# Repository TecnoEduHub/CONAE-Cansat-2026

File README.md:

# CANSAT 2026 — E.E.S.T. N.º5 "Amancio Williams"

Repositorio destinado a documentar el proceso de participación de la **Escuela de Educación Secundaria Técnica N.º 5 "Amancio Williams" de Mar del Plata** en el **Certamen CANSAT Secundario 2026**, organizado por la **Comisión Nacional de Actividades Espaciales (CONAE)**.

Este repositorio tiene como objetivo conservar el registro del proceso realizado por los estudiantes y docentes de la Técnica N.º 5.

La documentación irá incorporando progresivamente:

- Diseño conceptual.
- Documento Preliminar de Diseño.
- Investigación y antecedentes.
- Diseño electrónico.
- Programación y firmware.
- Diseño mecánico.
- Sistema de descenso.
- Misión primaria.
- Misión secundaria.
- Pruebas y validaciones.
- Fotografías y videos.
- Informes de avance.
- Problemas encontrados y soluciones adoptadas.
- Presentaciones y material de difusión.

La intención es que el repositorio no sea solamente un lugar donde almacenar el resultado final, sino una **bitácora técnica y educativa del proceso de aprendizaje**.

Durante la convocatoria, nuestra institución estuvo representada por dos equipos:

| Equipo | Resultado |
|---|---|
| **A.N.T.I.R.** | Actualmente en la **Etapa 4 — Construcción, seguimiento y validación** |
| **PENTA Space** | Llegó a la **Etapa 3 — Selección de proyectos y recepción del kit** |

Ambos equipos realizaron un excelente trabajo a lo largo de la competencia, atravesando un proceso de aprendizaje que involucró ciencia, electrónica, programación, diseño, experimentación, documentación y trabajo en equipo.

## ¿Qué es CANSAT?

**CANSAT** es una iniciativa educativa vinculada al ámbito espacial que propone a estudiantes de escuela secundaria asumir el desafío de diseñar, construir, probar y operar un **satélite a escala**.

El nombre surge de la combinación de las palabras **CAN** (lata) y **SAT** (satélite), debido a que la carga útil debe estar contenida dentro de un volumen aproximadamente equivalente al de una lata de gaseosa.

En Argentina, la convocatoria es organizada por la **Comisión Nacional de Actividades Espaciales (CONAE)** y busca acercar la ciencia y la tecnología a estudiantes de todo el país. El desafío reproduce, a pequeña escala, distintas etapas de una misión espacial: desde la concepción y el diseño hasta la construcción, validación, lanzamiento y operación del sistema.

Además del desarrollo tecnológico, la propuesta busca fortalecer competencias relacionadas con las disciplinas **STEM —Ciencia, Tecnología, Ingeniería y Matemáticas—**, promover el pensamiento científico y favorecer el trabajo colaborativo.

## El desafío

Cada equipo debe desarrollar una **carga útil** de dimensiones reducidas, contenida dentro de un cilindro de aproximadamente el tamaño de una lata.

El CANSAT es transportado mediante un cohete hasta una determinada altura y posteriormente desciende mediante un sistema de descenso controlado, generalmente un paracaídas. Durante el descenso debe realizar mediciones y transmitir los datos correspondientes a la misión.

La **misión primaria** establecida para CANSAT 2026 consiste en realizar, durante el descenso, un **sondeo atmosférico de presión y temperatura**.

La convocatoria también contempla una **misión secundaria**, mediante la cual cada equipo puede incorporar una actividad adicional. Para esta edición se propuso como objetivo la obtención de una imagen o video durante el lanzamiento, apogeo y/o trayectoria de descenso.

El desafío no consiste únicamente en construir un dispositivo electrónico. Los estudiantes deben trabajar como un verdadero equipo de misión: investigar, diseñar, programar, construir, documentar, realizar pruebas, analizar resultados y comunicar sus decisiones técnicas.

## Etapas de la convocatoria

La competencia se estructura en **cinco etapas eliminatorias**. Cada instancia debe ser aprobada para poder avanzar a la siguiente.

### Etapa 1 — Capacitación

Los estudiantes y docentes participan de una capacitación virtual destinada a incorporar los conocimientos, herramientas y materiales necesarios para desarrollar el proyecto.

La capacitación combina contenidos asincrónicos con instancias sincrónicas y finaliza con una evaluación.

### Etapa 2 — Diseño y presentación del proyecto

Cada equipo debe elaborar y presentar su propuesta.

Entre los principales entregables se encuentran:

- **Documento Preliminar de Diseño (DPD)**.
- **Video de presentación del equipo**.
- Descripción de la misión primaria y secundaria.
- Organización y roles de los integrantes.

La evaluación considera tanto el proyecto técnico como la capacidad del equipo para comunicar sus ideas.

### Etapa 3 — Selección y kit de materiales

Los proyectos son evaluados por un jurado y se seleccionan aquellos que resultan factibles, originales y que evidencian el compromiso y la capacidad de los equipos.

Los proyectos seleccionados reciben un **kit de materiales** para continuar con la construcción del CANSAT.

**Llegada del kit de materiales de CONAE a nuestra escuela.**

### Etapa 4 — Construcción, seguimiento y validación

Los equipos seleccionados construyen el prototipo diseñado y deben presentar diferentes evidencias de avance, incluyendo documentación, fotografías, videos y otros materiales solicitados.

Al finalizar esta instancia se realiza una validación mediante una videollamada con especialistas, en la que se presenta el prototipo y se revisa su funcionamiento.

De esta instancia se seleccionan los **cinco equipos** que participan de la campaña de lanzamiento, además de las correspondientes menciones especiales.

### Etapa 5 — Campaña de lanzamiento

Los cinco equipos seleccionados participan de la campaña de lanzamiento de sus CANSAT y realizan las mediciones correspondientes.

La convocatoria establece que los equipos seleccionados reciben cobertura de transporte, alojamiento y pensión completa para estudiantes y docentes responsables. 

## Nuestra participación

La Técnica N.º 5 tuvo la posibilidad de presentar **dos equipos** en CANSAT 2026, alcanzando ambos un desempeño destacado.

La convocatoria permite la participación de hasta dos equipos por institución. Cada equipo debe estar integrado por entre tres y cinco estudiantes y contar con el acompañamiento de un docente responsable.

### Equipo A.N.T.I.R.

**A.N.T.I.R.** es uno de los equipos representantes de la Escuela de Educación Secundaria Técnica N.º 5 "Amancio Williams".

El equipo actualmente logró avanzar hasta la:

> **Etapa 4 — Construcción, seguimiento y validación de los CANSAT**

Esto implicó superar las etapas iniciales de capacitación, presentación del proyecto y selección de propuestas, para luego recibir el kit de materiales y avanzar en la construcción y validación del prototipo.

En esta etapa el trabajo pasó del diseño conceptual a la implementación concreta: integración de hardware, programación, construcción mecánica, pruebas, documentación y preparación de las evidencias solicitadas por CONAE.

## Equipo PENTA Space

**PENTA Space** fue el segundo equipo que representó a la Técnica N.º 5 "Amancio Williams" en CANSAT 2026.

El equipo logró avanzar hasta la:

> **Etapa 3 — Selección de proyectos y envío del kit de materiales**

Esto significa que su propuesta superó las instancias iniciales de capacitación y evaluación del proyecto, alcanzando la selección que habilitaba a los equipos a continuar con el desarrollo del prototipo.

Aunque el recorrido de PENTA Space finalizó en esta etapa, su participación constituyó un importante proceso de aprendizaje y desarrollo de competencias técnicas y de trabajo en equipo.

## Resultados de la convocatoria

La edición 2026 contó con **257 equipos inscriptos**, de los cuales **120 presentaron su propuesta** mediante el Documento Preliminar de Diseño.

La evaluación estuvo a cargo de un jurado integrado por profesionales de la **Universidad Tecnológica Nacional (UTN)**, la **CONAE** y la **Asociación de Cohetería Experimental y Modelista de Argentina (ACEMA)**.

Los equipos ubicados entre los puestos 1 y 20 fueron invitados a pasar a la siguiente etapa, mientras que los puestos 21 al 40 recibieron una mención de honor por su destacada participación.

La propia organización destacó la elevada calidad de los trabajos presentados y lo ajustado de los puntajes obtenidos. 

## Criterios de evaluación

A lo largo de la convocatoria, los proyectos son evaluados considerando diferentes aspectos:

- **Admisibilidad:** cumplimiento de los requisitos formales.
- **Presentación:** calidad y cumplimiento de las entregas, organización del equipo y comunicación del proyecto.
- **Creatividad:** originalidad del diseño y de la misión secundaria.
- **Viabilidad:** factibilidad de realización y planificación de las pruebas.
- **Relevancia:** claridad, pertinencia, grado de avance y complejidad de la propuesta.

Estos criterios hacen que CANSAT sea mucho más que una competencia de construcción de un dispositivo: el proceso completo de planificación, documentación, validación y comunicación forma parte del desafío. 

## Recursos

- [Capacitación y videos del proyecto](https://drive.google.com/drive/folders/1EPjXjjoXwsOttx_nsDYTwsNPLpWK6ylc?usp=sharing)

- [Comisión Nacional de Actividades Espaciales](https://www.argentina.gob.ar/ciencia/conae)

- [Asociación de Cohetería Experimental y Modelista Argentina](https://www.acema.com.ar/)

## Agradecimientos

A la **Comisión Nacional de Actividades Espaciales (CONAE)** por impulsar esta propuesta educativa y brindar a estudiantes de escuelas secundarias de todo el país la posibilidad de acercarse al desarrollo de tecnología espacial.

A **ACEMA** y a todos los profesionales que participaron de la capacitación, evaluación y acompañamiento de los equipos.

Y, especialmente, a los estudiantes de **A.N.T.I.R.** y **PENTA Space**, por el compromiso, la creatividad, el trabajo técnico y la dedicación demostrados durante todo el proceso.

Independientemente de la etapa alcanzada por cada equipo, ambos representaron a la **Escuela de Educación Secundaria Técnica N.º 5** y dejaron un valioso registro de aprendizaje, experimentación y trabajo colaborativo.

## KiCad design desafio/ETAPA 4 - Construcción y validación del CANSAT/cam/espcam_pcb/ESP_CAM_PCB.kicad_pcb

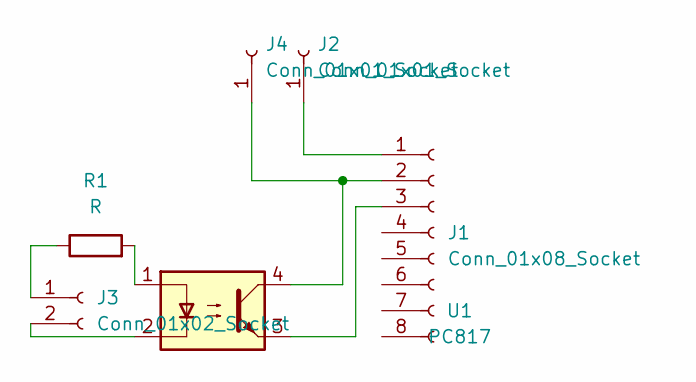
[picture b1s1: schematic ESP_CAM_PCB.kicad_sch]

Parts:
J1: Conn_01x08_Socket; PinSocket_1x08_P2.54mm_Vertical
J2, J4: Conn_01x01_Socket; PinSocket_1x01_P2.54mm_Vertical
J3: Conn_01x02_Socket; PinSocket_1x02_P2.54mm_Vertical
R1: R; R_Axial_DIN0207_L6.3mm_D2.5mm_P7.62mm_Horizontal
U1: PC817; DIP-4_W7.62mm

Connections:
unnamed: J1.1, J2.1 (Pin_1_1)
unnamed: J1.2, J4.1 (Pin_1_1), U1.4
unnamed: J1.3, U1.3
unnamed: J3.1, R1.1
unnamed: J3.2, U1.2
unnamed: R1.2, U1.1

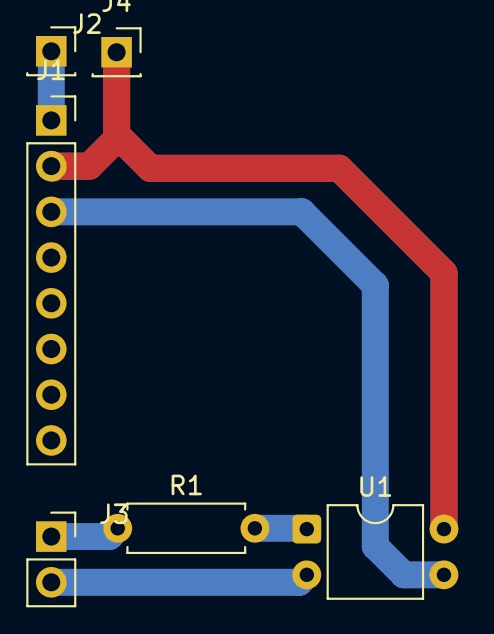
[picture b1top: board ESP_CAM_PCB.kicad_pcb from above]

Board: 2 copper layers, 6 parts (0 on the bottom side), 6 nets.

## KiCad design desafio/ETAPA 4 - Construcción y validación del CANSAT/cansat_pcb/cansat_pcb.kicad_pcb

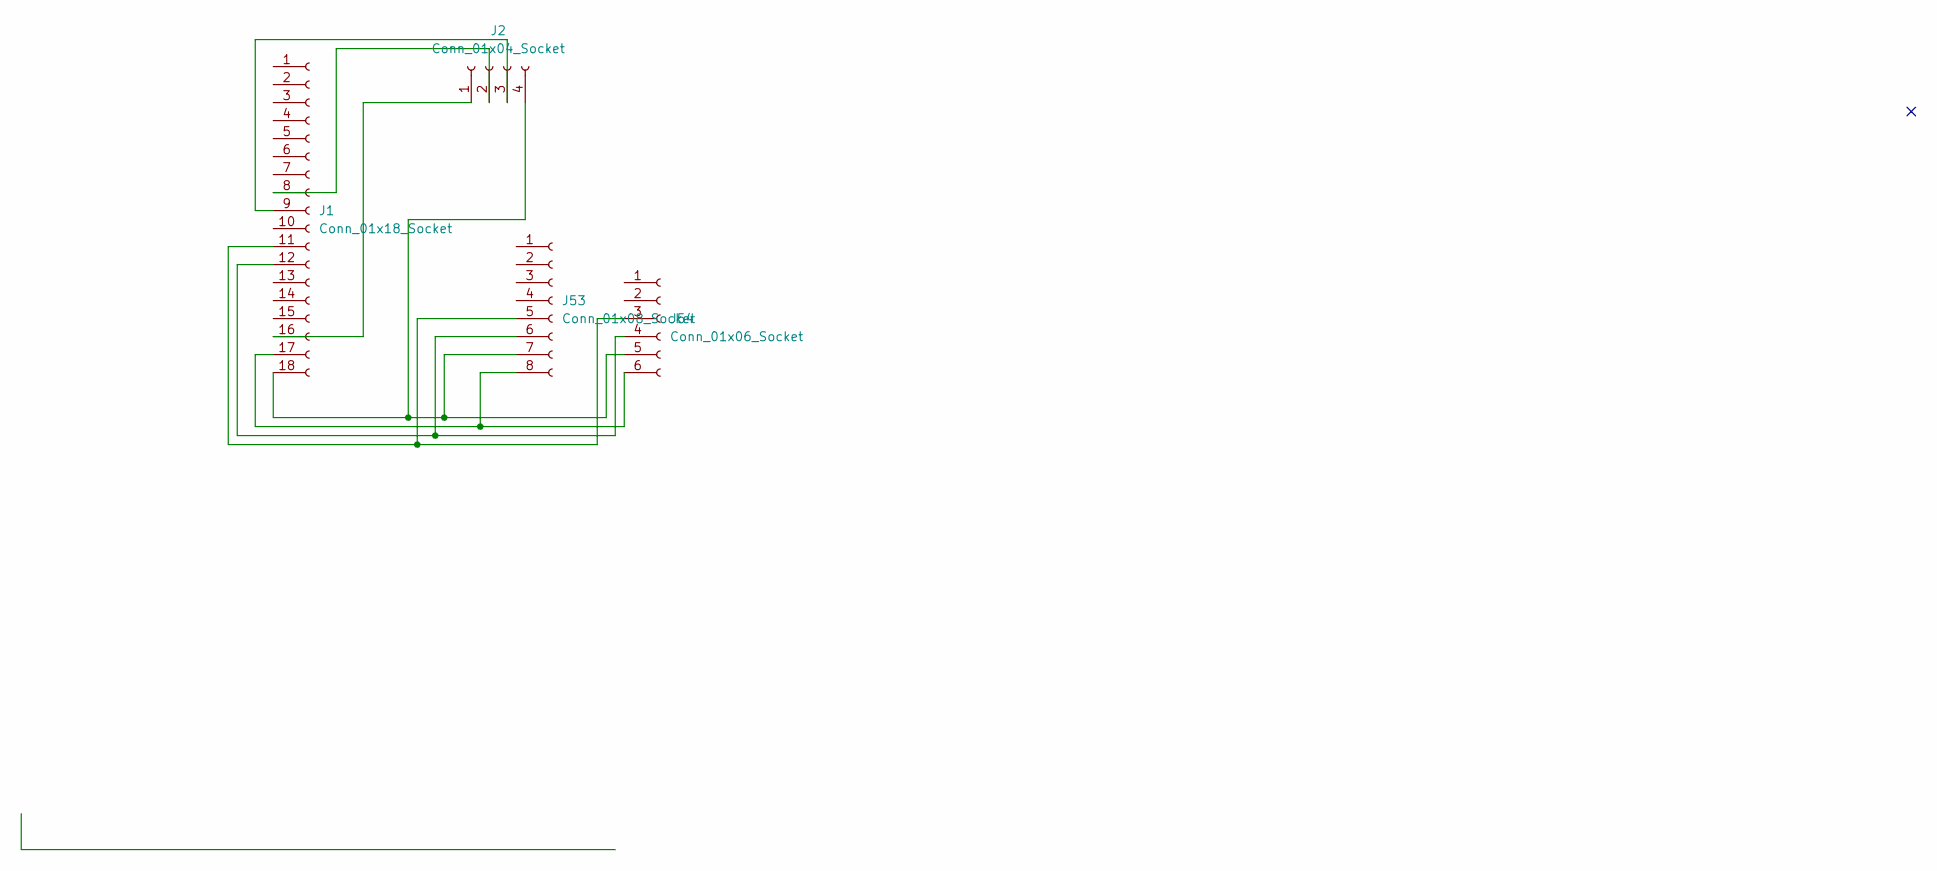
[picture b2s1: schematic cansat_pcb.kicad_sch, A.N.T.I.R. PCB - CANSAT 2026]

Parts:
J1: Conn_01x18_Socket; PinSocket_1x18_P2.54mm_Vertical
J2: Conn_01x04_Socket; PinHeader_1x04_P2.54mm_Vertical
J53: Conn_01x08_Socket; PinHeader_1x08_P2.54mm_Vertical
J54: Conn_01x06_Socket; PinHeader_1x06_P2.54mm_Vertical

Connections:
unnamed: J1.8, J2.2
unnamed: J1.9, J2.3
unnamed: J1.11, J53.5, J54.3
unnamed: J1.12, J53.6, J54.4
unnamed: J1.16, J2.1
unnamed: J1.17, J53.8, J54.6
unnamed: J1.18, J2.4, J53.7, J54.5

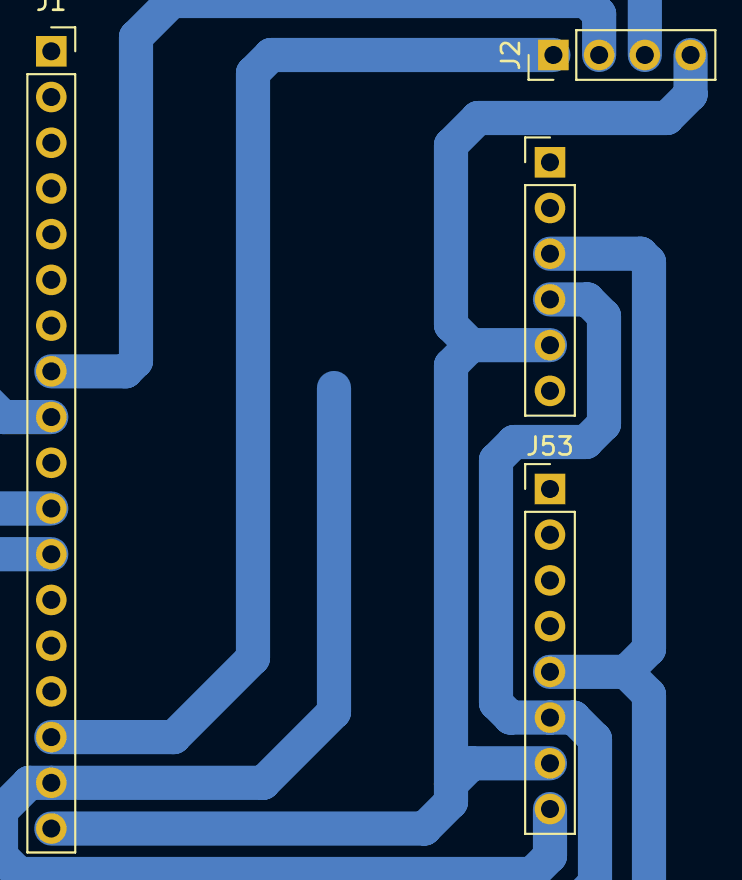
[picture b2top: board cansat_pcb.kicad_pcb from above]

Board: 2 copper layers, 4 parts (0 on the bottom side), 7 nets.
